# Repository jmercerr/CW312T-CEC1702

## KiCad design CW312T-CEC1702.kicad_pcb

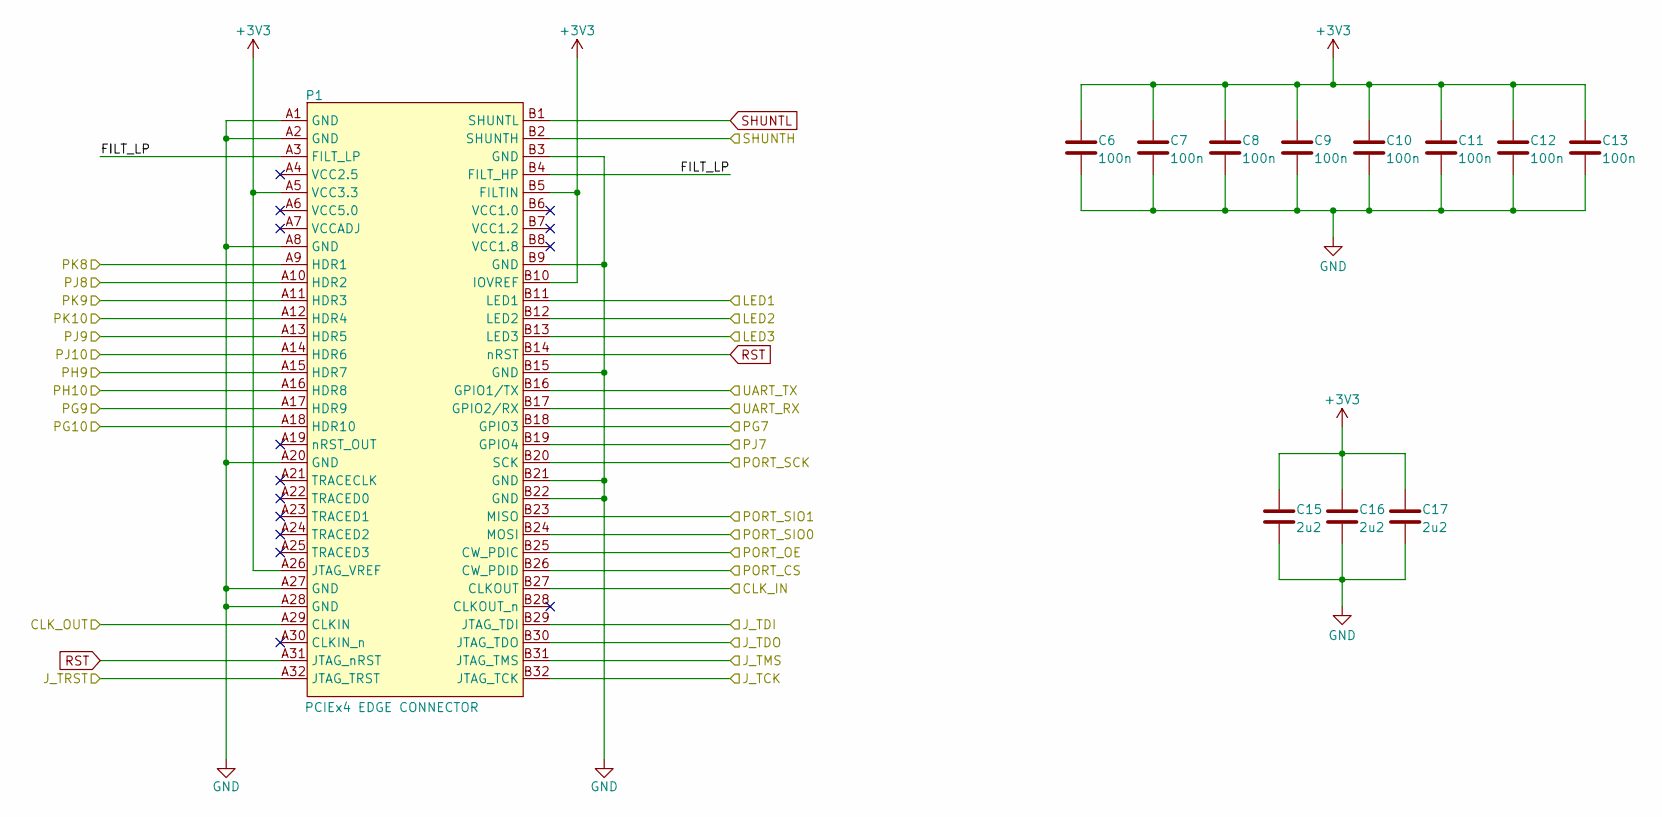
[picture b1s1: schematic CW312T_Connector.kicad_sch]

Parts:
C6, C7, C8, C9, C10, C11, C12, C13: CAP_100n_6.3V_0603; C_0603_1608Metric; Manufacturer Part Number CC0603KRX7R5BB104
C15, C16, C17: CAP_2u2_6.3V_0603; C_0603_1608Metric; Manufacturer Part Number CC0603KRX7R5BB225
P1: PCIEx4 EDGE CONNECTOR; CW312_Template

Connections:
+3V3: C6.2, C7.2, C8.2, C9.2, C10.2, C11.2, C12.2, C13.2, C15.2, C16.2, C17.2, P1.A5 (VCC3.3), P1.A26 (JTAG_VREF), P1.B5 (FILTIN), P1.B10 (IOVREF); also elsewhere on the board
/Active_Circuitry/CLK_IN: P1.B27 (CLKOUT); also elsewhere on the board
/Active_Circuitry/CLK_OUT: P1.A29 (CLKIN); also elsewhere on the board
/Active_Circuitry/J_TCK: P1.B32 (JTAG_TCK); also elsewhere on the board
/Active_Circuitry/J_TDI: P1.B29 (JTAG_TDI); also elsewhere on the board
/Active_Circuitry/J_TDO: P1.B30 (JTAG_TDO); also elsewhere on the board
/Active_Circuitry/J_TMS: P1.B31 (JTAG_TMS); also elsewhere on the board
/Active_Circuitry/J_TRST: P1.A32 (JTAG_TRST); also elsewhere on the board
/Active_Circuitry/LED1: P1.B11 (LED1); also elsewhere on the board
/Active_Circuitry/LED2: P1.B12 (LED2); also elsewhere on the board
/Active_Circuitry/LED3: P1.B13 (LED3); also elsewhere on the board
/Active_Circuitry/PG7: P1.B18 (GPIO3); also elsewhere on the board
/Active_Circuitry/PG9: P1.A17 (HDR9); also elsewhere on the board
/Active_Circuitry/PG10: P1.A18 (HDR10); also elsewhere on the board
/Active_Circuitry/PH9: P1.A15 (HDR7); also elsewhere on the board
/Active_Circuitry/PH10: P1.A16 (HDR8); also elsewhere on the board
/Active_Circuitry/PJ7: P1.B19 (GPIO4); also elsewhere on the board
/Active_Circuitry/PJ8: P1.A10 (HDR2); also elsewhere on the board
/Active_Circuitry/PJ9: P1.A13 (HDR5); also elsewhere on the board
/Active_Circuitry/PJ10: P1.A14 (HDR6); also elsewhere on the board
/Active_Circuitry/PK8: P1.A9 (HDR1); also elsewhere on the board
/Active_Circuitry/PK9: P1.A11 (HDR3); also elsewhere on the board
/Active_Circuitry/PK10: P1.A12 (HDR4); also elsewhere on the board
/Active_Circuitry/PORT_CS: P1.B26 (CW_PDID); also elsewhere on the board
/Active_Circuitry/PORT_OE: P1.B25 (CW_PDIC); also elsewhere on the board
/Active_Circuitry/PORT_SCK: P1.B20 (SCK); also elsewhere on the board
/Active_Circuitry/PORT_SIO0: P1.B24 (MOSI); also elsewhere on the board
/Active_Circuitry/PORT_SIO1: P1.B23 (MISO); also elsewhere on the board
/Active_Circuitry/SHUNTH: P1.B2 (SHUNTH); also elsewhere on the board
/Active_Circuitry/UART_RX: P1.B17 (GPIO2/RX); also elsewhere on the board
/Active_Circuitry/UART_TX: P1.B16 (GPIO1/TX); also elsewhere on the board
/CW312T_Connector/FILT_LP: P1.A3 (FILT_LP), P1.B4 (FILT_HP)
GND: C6.1, C7.1, C8.1, C9.1, C10.1, C11.1, C12.1, C13.1, C15.1, C16.1, C17.1, P1.A1 (GND), P1.A2 (GND), P1.A8 (GND), P1.A20 (GND), P1.A27 (GND), P1.A28 (GND), P1.B3 (GND), P1.B9 (GND), P1.B15 (GND), P1.B21 (GND), P1.B22 (GND); also elsewhere on the board
RST: P1.A31 (JTAG_nRST), P1.B14 (nRST); also elsewhere on the board
SHUNTL: P1.B1 (SHUNTL); also elsewhere on the board

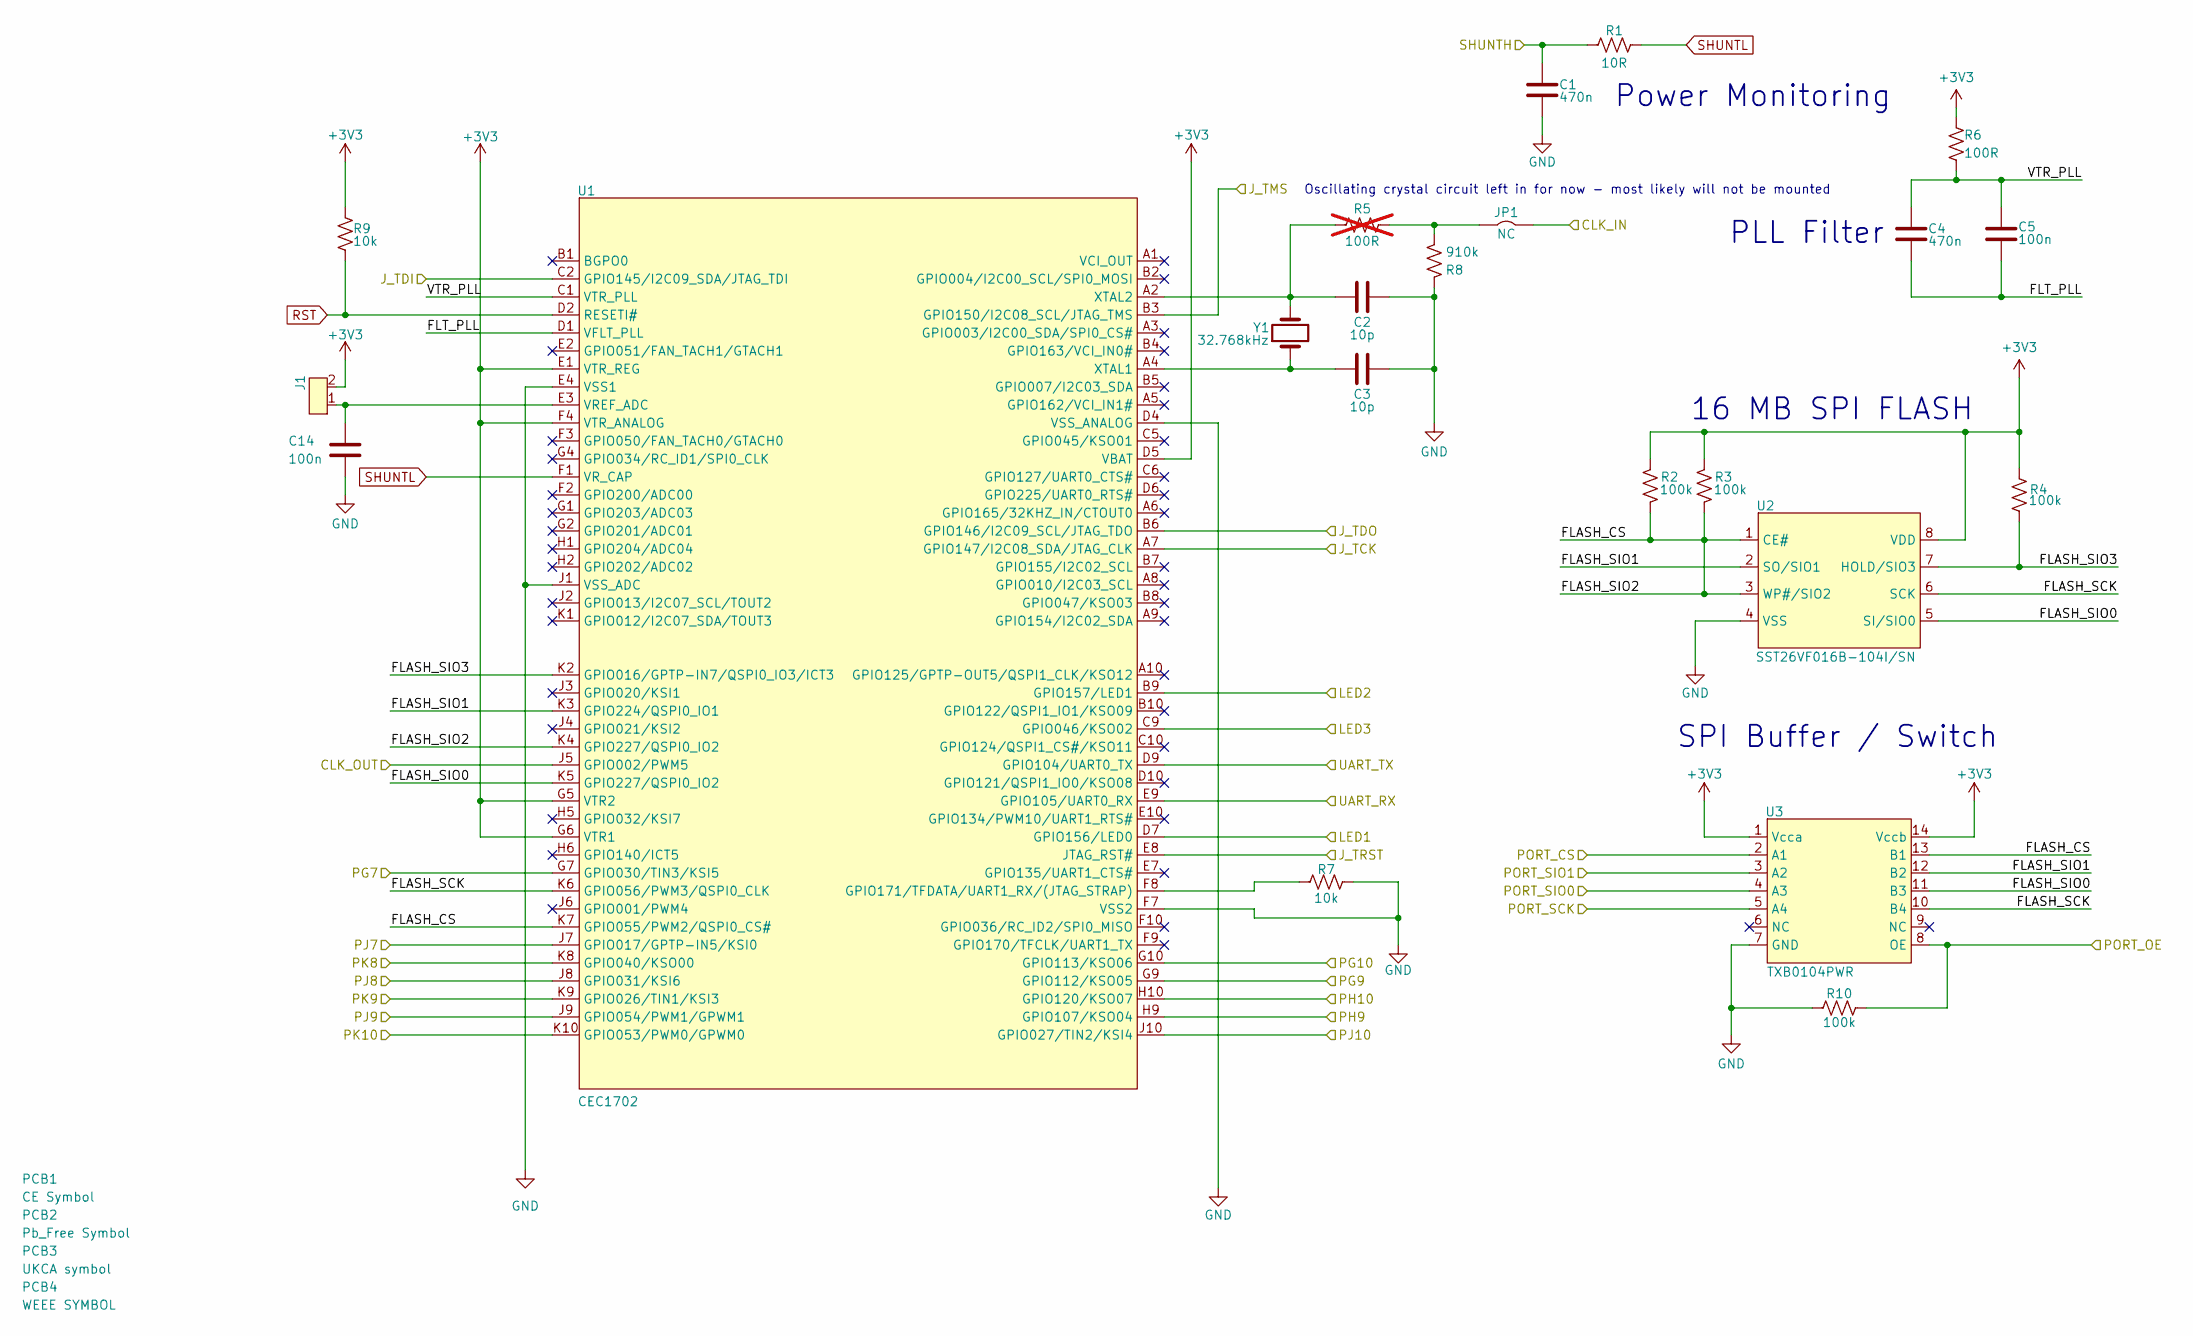
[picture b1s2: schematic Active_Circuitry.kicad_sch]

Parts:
C1, C4: CAP_470n_10V_0603; C_0603_1608Metric; Manufacturer Part Number CC0603KRX7R6BB474
C2, C3: CAP_10p_50V_0603; C_0603_1608Metric; Manufacturer Part Number CC0603JRNPO9BN100
C5: CAP_100n_6.3V_0603; C_0603_1608Metric; Manufacturer Part Number CC0603KRX7R5BB104
C14: CAP_100n_50V_0603; C_0603_1608Metric; Manufacturer Part Number CC0603KRX7R9BB104
J1: 2Pin_Header_2.54; PinHeader_2x01_P2.54mm_Vertical; Manufacturer Part Number M20-9990246
JP1: SolderJumper-2_P1.3mm_Bridged2Bar_Pad1.0x1.5mm
PCB1: CE Symbol; CE-Logo_8.5x6mm_SilkScreen
PCB2: Pb_Free Symbol; Pb_Free_8.0x8.0mm_SilkScreen
PCB3: UKCA symbol; UKCA-Logo_8x8mm_SilkScreen
PCB4: WEEE SYMBOL; WEEE-Logo_5.6x8mm_SilkScreen
R1: RES_10R_0603; R_0603_1608Metric; Manufacturer Part Number RC0603FR-0710RL
R2, R3, R4, R10: RES_100k_0603; R_0603_1608Metric; Manufacturer Part Number RC0603FR-07100KL
R5: RES_100R_0603; R_0603_1608Metric; Manufacturer Part Number RC0603FR-07100RL; not fitted
R6: RES_100R_0603; R_0603_1608Metric; Manufacturer Part Number RC0603FR-07100RL
R7, R9: RES_10k_0603; R_0603_1608Metric; Manufacturer Part Number RC0603FR-0710KL
R8: RES_910k_0603; R_0603_1608Metric; Manufacturer Part Number RC0603FR-07910KL
U1: CEC1702; BGA84C65P10X10_700X700X80; Manufacturer Part Number CEC1702Q-B1-SX-TR
U2: SST26VF016B-104I/SN; SOIC-8_3.9x4.9mm_P1.27mm; Manufacturer Part Number SST26VF016B-104I/SN
U3: TXB0104PWR; SOIC-14_3.9x8.7mm_P1.27mm; Manufacturer Part Number TXB0104PWR
Y1: 32.768kHz; Crystal_SMD_3215-2Pin_3.2x1.5mm; Manufacturer Part Number FC-135 32.7680KA-K0

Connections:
+3V3: J1.2, R2.2, R3.2, R4.1, R6.2, R9.2, U1.D5 (VBAT), U1.E1 (VTR_REG), U1.F4 (VTR_ANALOG), U1.G5 (VTR2), U1.G6 (VTR1), U2.8 (VDD), U3.1 (Vcca), U3.14 (Vccb); also elsewhere on the board
/Active_Circuitry/CLK_IN: JP1.1; also elsewhere on the board
/Active_Circuitry/CLK_OUT: U1.J5 (GPIO002/PWM5); also elsewhere on the board
/Active_Circuitry/FLASH_CS: R2.1, R3.1, U1.K4 (GPIO227/QSPI0_IO2), U1.K7 (GPIO055/PWM2/QSPI0_CS#), U2.1 (CE#), U2.3 (WP#/SIO2), U3.13 (B1)
/Active_Circuitry/FLASH_SCK: U1.K6 (GPIO056/PWM3/QSPI0_CLK), U2.6 (SCK), U3.10 (B4)
/Active_Circuitry/FLASH_SIO0: U1.K5 (GPIO227/QSPI0_IO2), U2.5 (SI/SIO0), U3.11 (B3)
/Active_Circuitry/FLASH_SIO1: U1.K3 (GPIO224/QSPI0_IO1), U2.2 (SO/SIO1), U3.12 (B2)
/Active_Circuitry/FLASH_SIO3: R4.2, U1.K2 (GPIO016/GPTP-IN7/QSPI0_IO3/ICT3), U2.7 (HOLD/SIO3)
/Active_Circuitry/FLT_PLL: C4.1, C5.1, U1.D1 (VFLT_PLL)
/Active_Circuitry/J_TCK: U1.A7 (GPIO147/I2C08_SDA/JTAG_CLK); also elsewhere on the board
/Active_Circuitry/J_TDI: U1.C2 (GPIO145/I2C09_SDA/JTAG_TDI); also elsewhere on the board
/Active_Circuitry/J_TDO: U1.B6 (GPIO146/I2C09_SCL/JTAG_TDO); also elsewhere on the board
/Active_Circuitry/J_TMS: U1.B3 (GPIO150/I2C08_SCL/JTAG_TMS); also elsewhere on the board
/Active_Circuitry/J_TRST: U1.E8 (JTAG_RST#); also elsewhere on the board
/Active_Circuitry/LED1: U1.D7 (GPIO156/LED0); also elsewhere on the board
/Active_Circuitry/LED2: U1.B9 (GPIO157/LED1); also elsewhere on the board
/Active_Circuitry/LED3: U1.C9 (GPIO046/KSO02); also elsewhere on the board
/Active_Circuitry/PG7: U1.G7 (GPIO030/TIN3/KSI5); also elsewhere on the board
/Active_Circuitry/PG9: U1.G9 (GPIO112/KSO05); also elsewhere on the board
/Active_Circuitry/PG10: U1.G10 (GPIO113/KSO06); also elsewhere on the board
/Active_Circuitry/PH9: U1.H9 (GPIO107/KSO04); also elsewhere on the board
/Active_Circuitry/PH10: U1.H10 (GPIO120/KSO07); also elsewhere on the board
/Active_Circuitry/PJ7: U1.J7 (GPIO017/GPTP-IN5/KSI0); also elsewhere on the board
/Active_Circuitry/PJ8: U1.J8 (GPIO031/KSI6); also elsewhere on the board
/Active_Circuitry/PJ9: U1.J9 (GPIO054/PWM1/GPWM1); also elsewhere on the board
/Active_Circuitry/PJ10: U1.J10 (GPIO027/TIN2/KSI4); also elsewhere on the board
/Active_Circuitry/PK8: U1.K8 (GPIO040/KSO00); also elsewhere on the board
/Active_Circuitry/PK9: U1.K9 (GPIO026/TIN1/KSI3); also elsewhere on the board
/Active_Circuitry/PK10: U1.K10 (GPIO053/PWM0/GPWM0); also elsewhere on the board
/Active_Circuitry/PORT_CS: U3.2 (A1); also elsewhere on the board
/Active_Circuitry/PORT_OE: R10.2, U3.8 (OE); also elsewhere on the board
/Active_Circuitry/PORT_SCK: U3.5 (A4); also elsewhere on the board
/Active_Circuitry/PORT_SIO0: U3.4 (A3); also elsewhere on the board
/Active_Circuitry/PORT_SIO1: U3.3 (A2); also elsewhere on the board
/Active_Circuitry/SHUNTH: C1.2, R1.1; also elsewhere on the board
/Active_Circuitry/UART_RX: U1.E9 (GPIO105/UART0_RX); also elsewhere on the board
/Active_Circuitry/UART_TX: U1.D9 (GPIO104/UART0_TX); also elsewhere on the board
/Active_Circuitry/VTR_PLL: C4.2, C5.2, R6.1, U1.C1 (VTR_PLL)
GND: C1.1, C2.2, C3.2, C14.1, R7.2, R8.2, R10.1, U1.D4 (VSS_ANALOG), U1.E4 (VSS1), U1.F7 (VSS2), U1.J1 (VSS_ADC), U2.4 (VSS), U3.7 (GND); also elsewhere on the board
unnamed: JP1.2, R5.2, R8.1
unnamed: R7.1, U1.F8 (GPIO171/TFDATA/UART1_RX/(JTAG_STRAP))
unnamed: C14.2, J1.1, U1.E3 (VREF_ADC)
unnamed: C3.1, U1.A4 (XTAL1), Y1.1
unnamed: C2.1, R5.1, U1.A2 (XTAL2), Y1.2
RST: R9.1, U1.D2 (RESETI#); also elsewhere on the board
SHUNTL: R1.2, U1.F1 (VR_CAP); also elsewhere on the board

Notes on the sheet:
PLL Filter
16 MB SPI FLASH
Power Monitoring
Oscillating crystal circuit left in for now - most likely will not be mounted
SPI Buffer / Switch

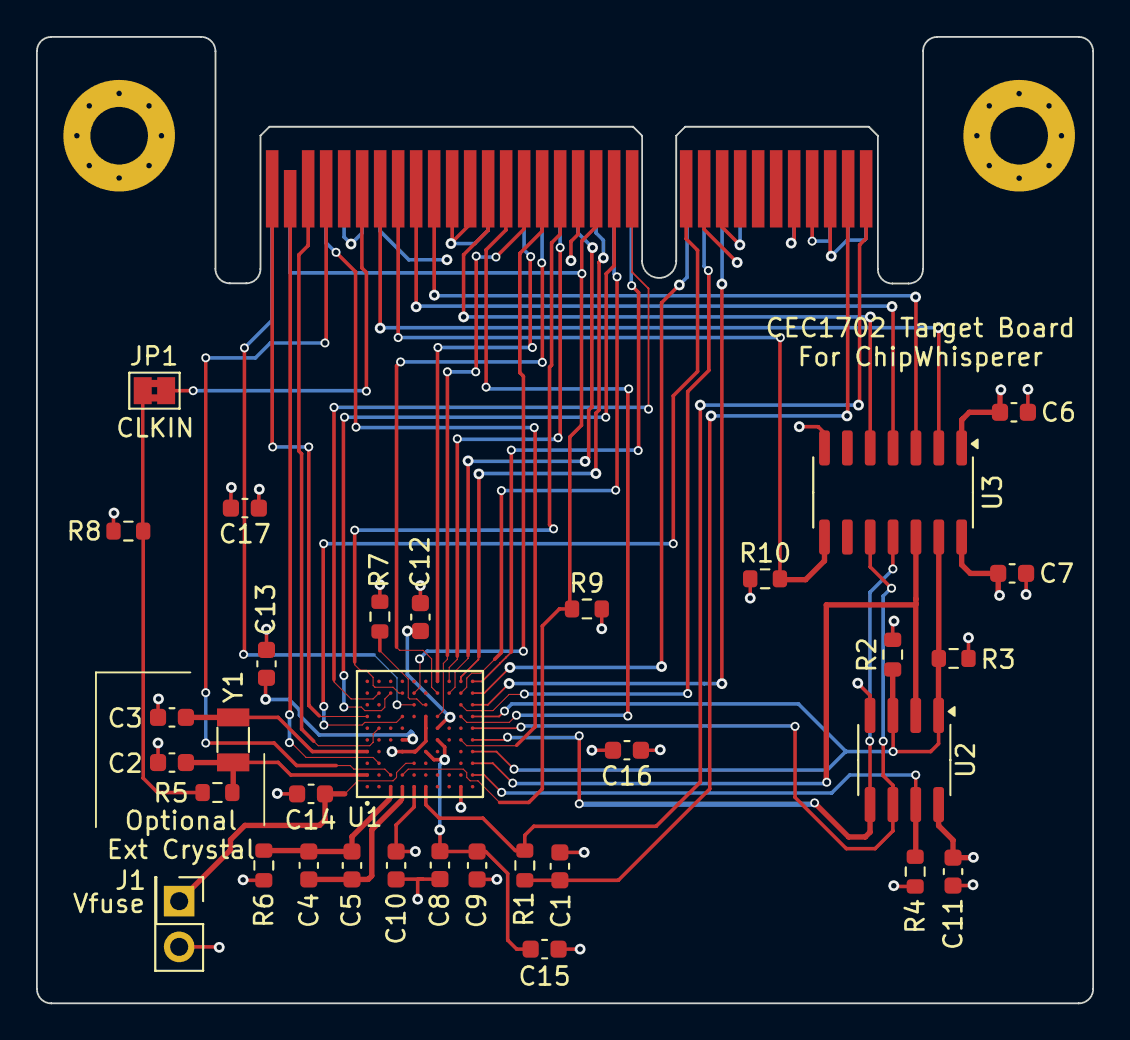
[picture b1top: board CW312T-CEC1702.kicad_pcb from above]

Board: 4 copper layers, 58.7 x 53.7 mm, 38 parts (0 on the bottom side), 47 nets.

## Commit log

2024-12-13 updated pcb, schematic, production files
2024-12-19 updated schematic and pcb after library re-organization
